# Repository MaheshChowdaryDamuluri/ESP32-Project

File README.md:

# 📡 Custom ESP32 Microcontroller Core PCB Design Project

Welcome to the official repository for the **Custom ESP32 System Breakout Hardware** project. This repository contains the complete programmatic schematic architectures, optimal 2-layer routing layouts, and fabrication-ready source files engineered entirely within the KiCad design suite.

This design focuses on optimizing power-rail decoupling loops for high-frequency RF applications, providing accessible interface headers for peripheral integration, and stabilizing programming pathways.

---

## 📐 1. Technical System Architecture

The hardware layout systematically segments power domains, USB transceiver configurations, and the core wireless MCU footprint to eliminate trace interference and parasitic noise loops:

### 🧠 Core Wireless Processor Node (`esp-32.kicad_sch`)
* **Module Core:** Features an **ESP32 WROOM Series** surface-mount processing module incorporating dual-core processing power and integrated Wi-Fi/Bluetooth capabilities.
* **Thermal Management:** Optimized using a dense matrix of twelve **0.2 mm thermal stitching vias** embedded directly inside the main central ground pad (`Pad 41`) to transfer module heat to the bottom ground plane.
* **Pin Configuration:** All active GPIO and system interface boundaries are routed symmetrically out to external pin headers for straightforward probing and instrumentation.

### 🔌 USB Telemetry & Serial Communications Array
* **Interface Bridge:** Implements a rugged hardware connection utilizing a specialized 16-pin USB Type-C receptacle interface (`J1`).
* **Signal Integrity:** USB differential pairs ($D+$ and $D-$) are tightly routed with specific trace geometry to prevent data cross-talk during rapid code flashing and debugging streams.

### ⚡ Power Management & Multi-Stage Decoupling
* **LDO Step-Down Topology:** Incorporates an **LM1117-5.0 Low-Dropout Linear Regulator** (`U2`) converting external incoming $V_{BUS}$ power cleanly down to system supply rails.
* **Filtering Network:** Employs a robust decoupling capacitor arrangement combining high-frequency $0.1\mu\text{F}$ surface-mount bypass capacitors right at the power input pins with larger bulk smoothing capacitors ($1\mu\text{F}$ and high-capacitance targets) to prevent supply voltage dips during transient RF current spikes.

---

## 🛠️ 2. PCB Layout & Manufacturing Disciplines

The board transitions from complex multi-layer configurations down to a highly optimized, cost-efficient **2-Layer PCB Architecture** satisfying precise industrial manufacturing constraints:

1. **Top Layer (`F.Cu`):** Handles primary component landings, high-speed signal routing traces, and localized power distribution tracks.
2. **Bottom Layer (`B.Cu`):** Serving as a continuous, low-impedance solid Ground Plane (`GND`) to significantly reduce electromagnetic emissions and secure return current paths.

* **⚙️ Design Constraints Cleared:** The board setup file is tuned to a high-density standard with a minimum global trace/pad clearance of **0.15 mm** and an ultra-fine **0.2 mm minimum hole / via drill limit** to handle small component pitches perfectly.
* **🎨 Silkscreen & Layout Visuals:** Clear, detailed layer mapping for text indicators to ensure easy component identification during manual assembly.

---

## 📋 3. Project Bill of Materials (BOM)

| Designator | Component Quantity | Component Value | Package Footprint | Purpose / Function |
| :--- | :---: | :--- | :--- | :--- |
| **U1** | 1 | ESP32 Module | Custom QFN-style SMD | Primary Dual-Core Wi-Fi/BT MCU Core |
| **U2** | 1 | LM1117-5.0 | SOT-223 / Equivalent | Main Low-Dropout Voltage Regulator |
| **J1** | 1 | USB_C_Receptacle_16P | USB4105-xx-A_16P_Horizontal | Main Power Input & Telemetry Interface |
| **SW1, SW2** | 2 | SW_Push | Tactile Switch 2-Pin | Flash Enable and System Master Reset |
| **C3** | 1 | 1uF / Chosen Value | C_1206_3216Metric | Input Voltage Bulk Filter Capacitor |
| **C5** | 1 | Chosen Filter Value | C_0805_2012Metric | Output Power Line Smoothing Filter |
| **C6** | 1 | Decoupling Value | C_1210_3225Metric | High-Frequency Bypass Filter Passive |
| **R3** | 1 | Current Limiter | R_0805_2012Metric | System Pull-up/Pull-down Configuration |

---

## 📂 4. Repository File Directory
```text
├── esp-32.kicad_pro    # Master project parameters tracking file links and layer limits
├── esp-32.kicad_sch    # Complete electrical circuit schematics and net labels
├── esp-32.kicad_pcb    # Completed physical 2-layer trace routing layout file
├── .gitignore          # Automatically ignores background autosaves and backup zip files
└── README.md           # This comprehensive documentation and specifications file

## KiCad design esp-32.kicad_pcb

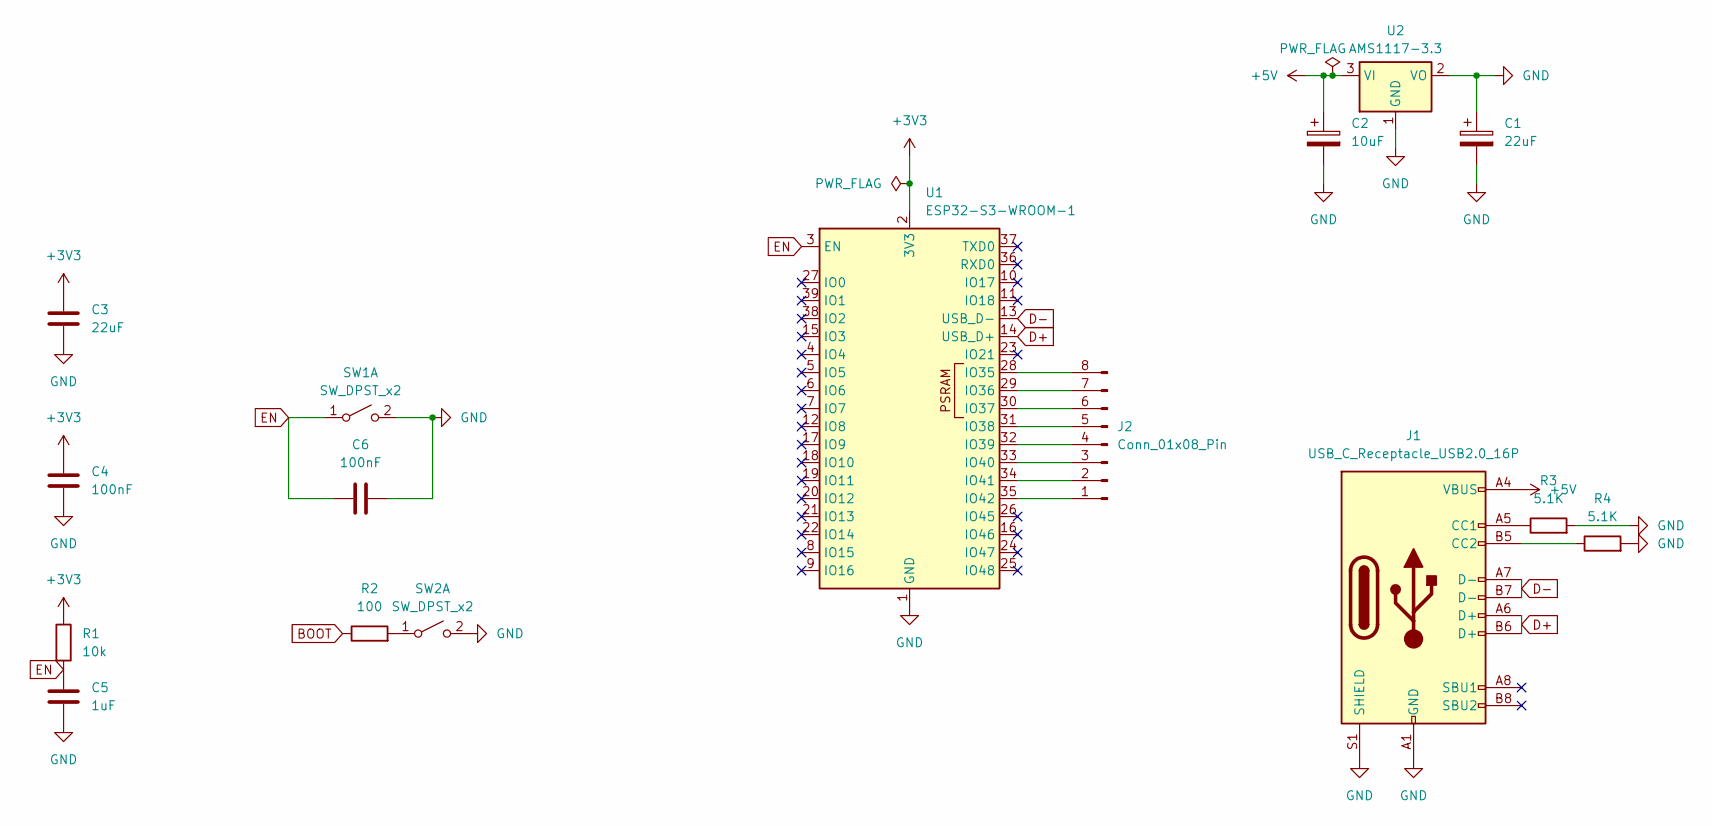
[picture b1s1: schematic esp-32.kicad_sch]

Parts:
C1: 22uF; CP_Elec_6.3x5.4
C2: 10uF; CP_Elec_5x5.4
C3: 22uF; C_1206_3216Metric
C4, C6: 100nF; C_1210_3225Metric
C5: 1uF; C_0805_2012Metric
J1: USB_C_Receptacle_USB2.0_16P; USB_C_Receptacle_GCT_USB4105-xx-A_16P_TopMnt_Horizontal
J2: Conn_01x08_Pin; PinHeader_1x08_P1.00mm_Vertical
R1: 10k; R_0805_2012Metric
R2: 100; R_0805_2012Metric
R3, R4: 5.1K; R_0805_2012Metric
SW1, SW2: SW_DPST_x2; SW_CK_JS202011CQN_DPDT_Straight
U1: ESP32-S3-WROOM-1
U2: AMS1117-3.3; SOT-223-3_TabPin2

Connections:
+3V3: C3.1, C4.1, R1.1, U1.2 (3V3)
+5V: C2.1, J1.A4 (VBUS), J1.A9 (VBUS), J1.B4 (VBUS), J1.B9 (VBUS), U2.3 (VI)
BOOT: R2.1
D+: J1.A6 (D+), J1.B6 (D+), U1.14 (USB_D+)
D-: J1.A7 (D-), J1.B7 (D-), U1.13 (USB_D-)
EN: C5.1, C6.1, R1.2, SW1.1 (A), U1.3 (EN)
GND: C1.1, C1.2, C2.2, C3.2, C4.2, C5.2, C6.2, J1.A1 (GND), J1.A12 (GND), J1.B1 (GND), J1.B12 (GND), J1.S1 (SHIELD), R3.2, R4.2, SW1.2 (B), SW2.2 (B), U1.1 (GND), U1.40 (GND), U1.41 (GND), U2.1 (GND), U2.2 (VO)
unnamed: J1.A5 (CC1), R3.1
unnamed: J1.B5 (CC2), R4.1
unnamed: J2.1, U1.35 (IO42)
unnamed: J2.2, U1.34 (IO41)
unnamed: J2.3, U1.33 (IO40)
unnamed: J2.4, U1.32 (IO39)
unnamed: J2.5, U1.31 (IO38)
unnamed: J2.6, U1.30 (IO37)
unnamed: J2.7, U1.29 (IO36)
unnamed: J2.8, U1.28 (IO35)
unnamed: R2.2, SW2.1 (A)

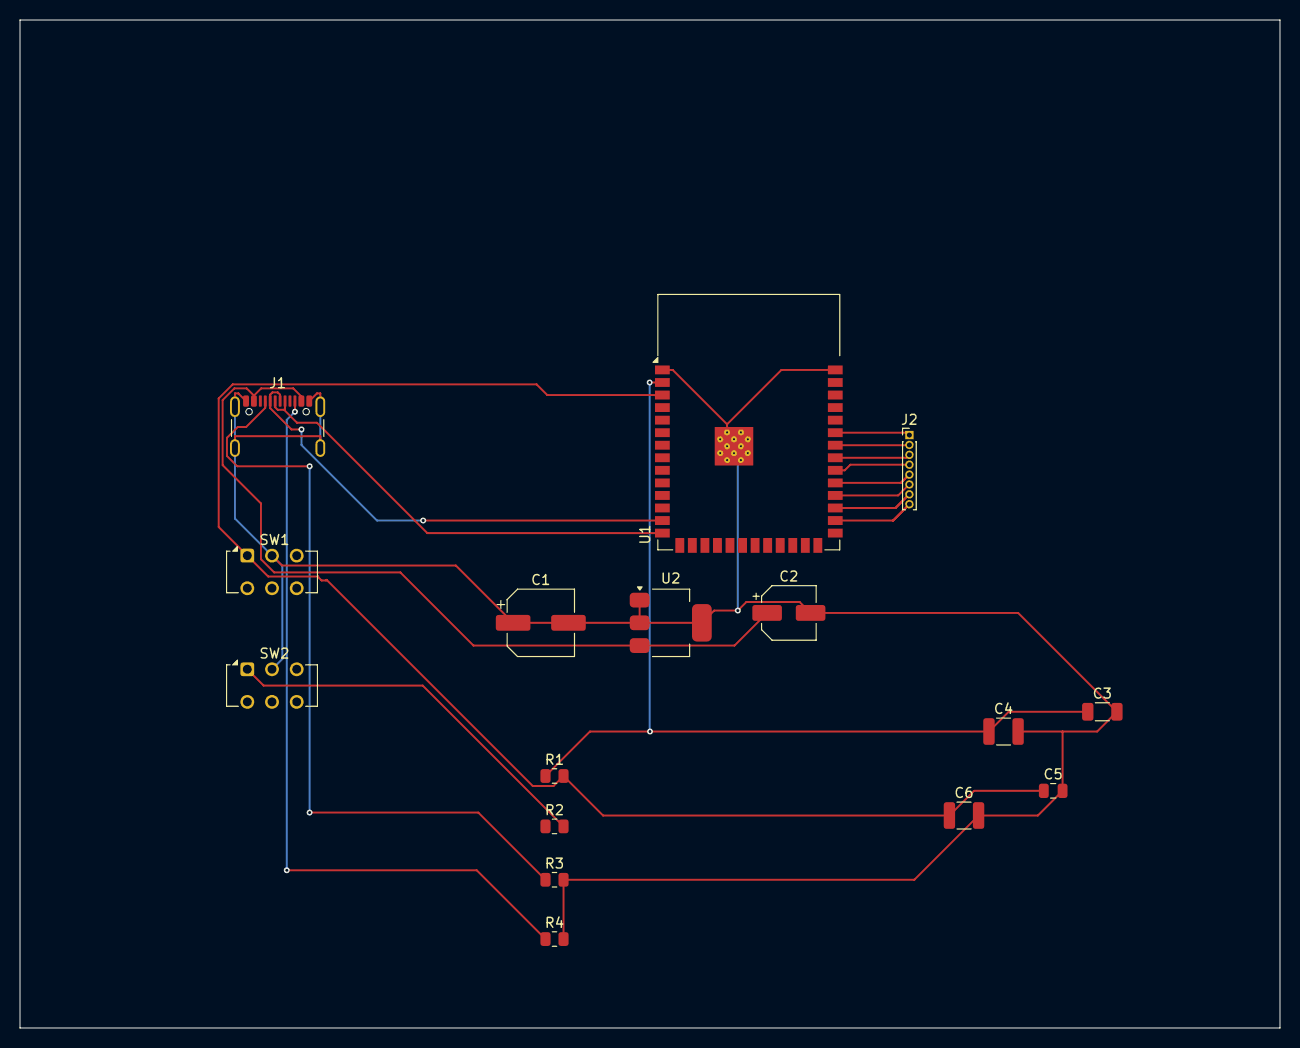
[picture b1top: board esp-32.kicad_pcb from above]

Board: 2 copper layers, 127.5 x 102.0 mm, 16 parts (0 on the bottom side), 17 nets.
